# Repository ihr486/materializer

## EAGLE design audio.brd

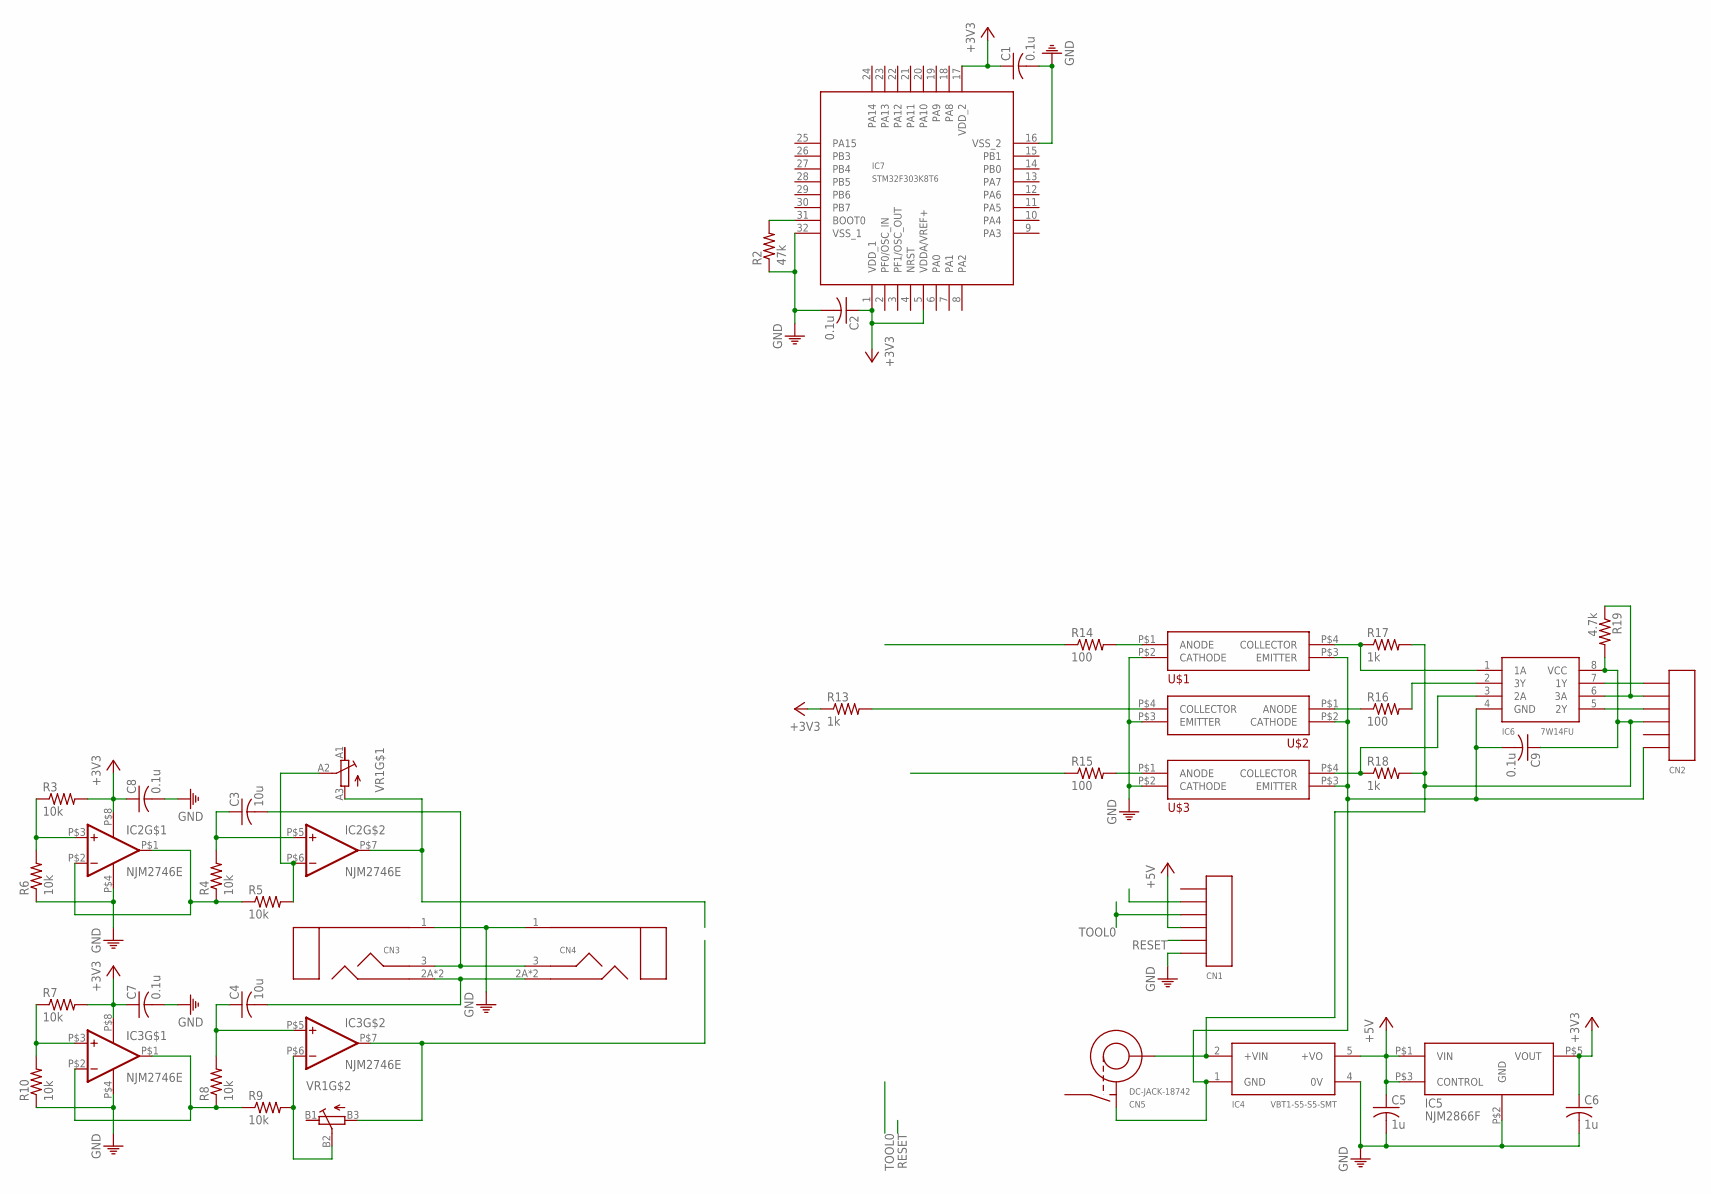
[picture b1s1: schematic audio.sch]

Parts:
C1, C2, C7, C8, C9: 0.1u; C2012
C3, C4: 10u; C2012
C5, C6: 1u; C2012
CN1: PH-1X06SG
CN2: PH-1X06RG
CN3, CN4: STEREO-3.5-MJ8435; MJ8435
CN5: DC-JACK-18742; 18742
IC2, IC3: NJM2746E; EMP8
IC4: VBT1-S5-S5-SMT
IC5: NJM2866F; SOT-23-5
IC6: 7W14FU; SSOP8-P-0.65
IC7: STM32F303K8T6; P-LQFP32-7X7-0.80
R2: 47k; R2012
R3, R4, R5, R6, R7, R8, R9, R10: 10k; R2012
R13, R17, R18: 1k; R2012
R14, R15, R16: 100; R2012
R19: 4.7k; R2012
U$1, U$2, U$3: TLP291; 11-3C1
VR1: R-TRIM-RK0971220; RK0971220-F15-C0-A104

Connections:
+3V3: C1.1, C2.1, C6.1, C7.1, C8.1, IC2.P$8 (V+), IC3.P$8 (V+), IC5.P$5 (VOUT), IC7.1 (VDD_1), IC7.5 (VDDA/VREF+), IC7.17 (VDD_2), R3.2, R7.2, R13.1
+5V: C5.1, CN1.P$4, IC4.5 (+VO), IC5.P$1 (VIN), IC5.P$3 (CONTROL)
GND: C1.2, C2.2, C5.2, C6.2, C7.2, C8.2, CN1.P$6, CN3.1 (SLEEVE), CN4.1 (SLEEVE), IC2.P$4 (V-), IC3.P$4 (V-), IC4.4 (0V), IC5.P$2 (GND), IC7.16 (VSS_2), IC7.32 (VSS_1), R2.1, R6.1, R10.1, U$1.P$2 (CATHODE), U$2.P$3 (EMITTER), U$3.P$2 (CATHODE)
unnamed: IC2.P$1 (OUT), IC2.P$2 (-IN), R4.1, R5.1
unnamed: IC7.31 (BOOT0), R2.2
unnamed: C3.2, CN3.3 (RING), CN4.3 (RING)
unnamed: C3.1, IC2.P$5 (+IN), R4.2
unnamed: IC2.P$3 (+IN), R3.1, R6.2
unnamed: C9.2, CN2.P$6, CN5.P$2 (TIP), IC4.1 (GND), IC6.4 (GND), U$1.P$3 (EMITTER), U$2.P$2 (CATHODE), U$3.P$3 (EMITTER)
unnamed: C9.1, CN2.P$4, CN5.P$1 (CENTER), IC4.2 (+VIN), IC6.8 (VCC), R17.2, R18.2, R19.2
unnamed: IC2.P$6 (-IN), R5.2, VR1.A2 (S)
unnamed: IC2.P$7 (OUT), VR1.A3 (E)
unnamed: IC3.P$1 (OUT), IC3.P$2 (-IN), R8.1, R9.1
unnamed: IC3.P$3 (+IN), R7.1, R10.2
unnamed: C4.1, IC3.P$5 (+IN), R8.2
unnamed: IC3.P$6 (-IN), R9.2, VR1.B2 (S)
unnamed: C4.2, CN3.2A (TIP), CN3.2B (TIP), CN4.2A (TIP), CN4.2B (TIP)
unnamed: IC3.P$7 (OUT), VR1.B3 (E)
unnamed: R13.2, U$2.P$4 (COLLECTOR)
unnamed: R14.2, U$1.P$1 (ANODE)
unnamed: IC6.3 (2A), R18.1, U$3.P$4 (COLLECTOR)
unnamed: R15.2, U$3.P$1 (ANODE)
unnamed: R16.1, U$2.P$1 (ANODE)
unnamed: CN2.P$1, IC6.7 (1Y)
unnamed: IC6.1 (1A), R17.1, U$1.P$4 (COLLECTOR)
unnamed: CN2.P$2, IC6.6 (3A), R19.1
unnamed: CN2.P$3, IC6.5 (2Y)
unnamed: IC6.2 (3Y), R16.2
RESET: CN1.P$5
TOOL0: CN1.P$3

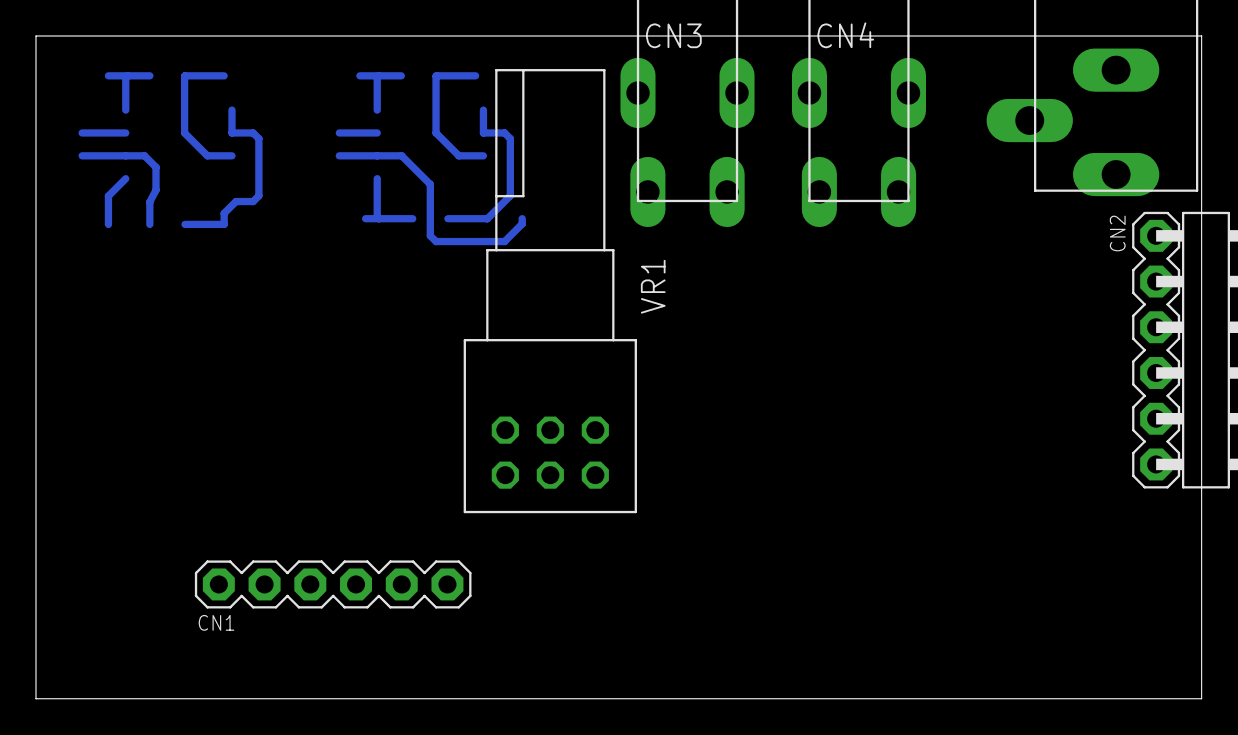
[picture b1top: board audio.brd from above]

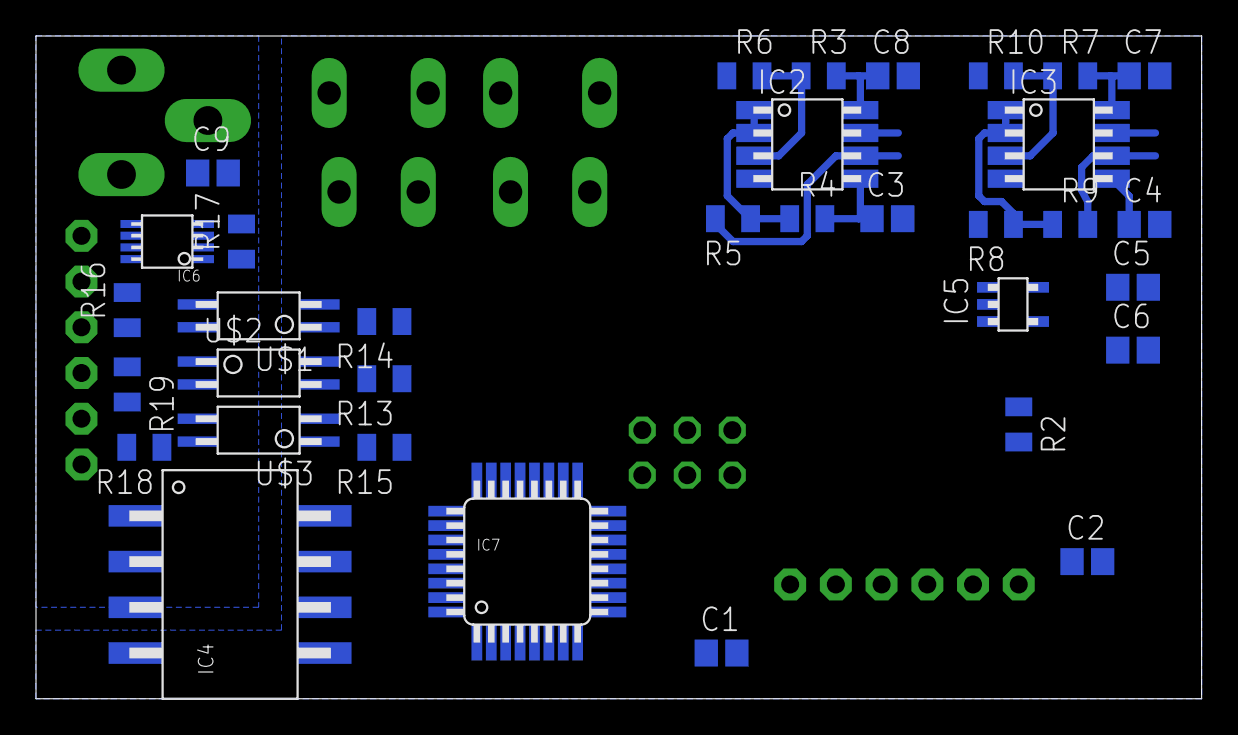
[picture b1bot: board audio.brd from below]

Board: 2 copper layers, 64.8 x 36.8 mm, 40 parts (34 on the bottom side), 28 nets.

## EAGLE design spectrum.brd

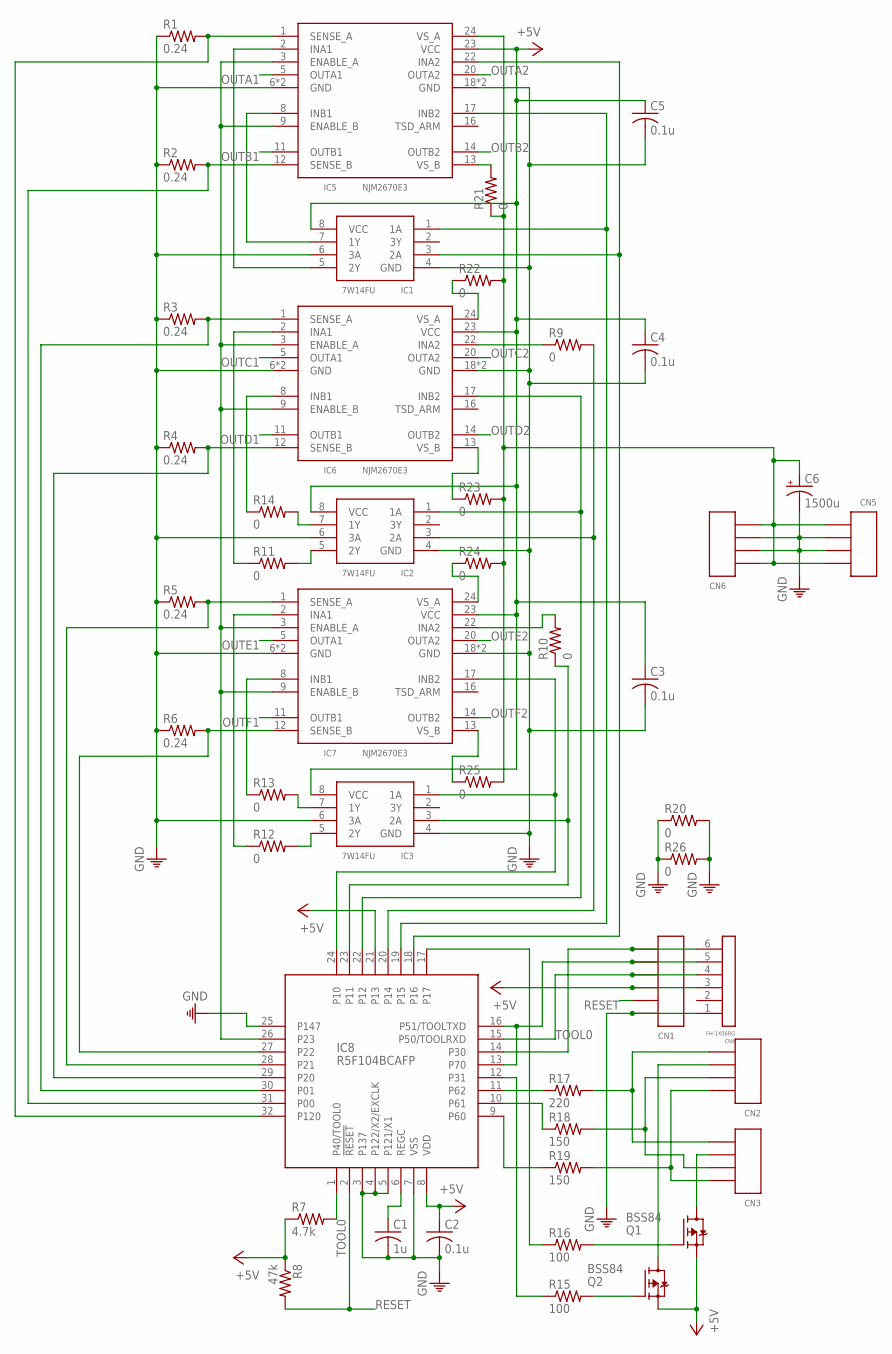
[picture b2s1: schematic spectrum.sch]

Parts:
C1: 1u; C2012
C2, C3, C4, C5: 0.1u; C2012
C6: 1500u; E3,5-8
CN1: PH-1X06RG
CN2, CN3: PH-1X04SG
CN4: FH-1X06RG
CN5: PH-1X04SGRG; PH-1X04RG
CN6: FH-1X04RG
IC1, IC2, IC3: 7W14FU; SSOP8-P-0.65
IC5, IC6, IC7: NJM2670E3; EMP-24
IC8: R5F104BCAFP; P-LQFP32-7X7-0.80
Q1, Q2: BSS84; SOT-23F
R1, R2, R3, R4, R5, R6: 0.24; R3225
R7: 4.7k; R2012
R8: 47k; R2012
R9, R10, R11, R12, R13, R14: 0; R2012
R15, R16: 100; R2012
R17: 220; R2012
R18, R19: 150; R2012
R20, R26: 0; 0204/5
R21, R22, R23, R24, R25: 0; 0204/7

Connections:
+5V: C2.1, C3.1, C4.1, C5.1, CN1.P$4, CN4.3, IC1.8 (VCC), IC2.8 (VCC), IC3.8 (VCC), IC5.23 (VCC), IC6.23 (VCC), IC7.23 (VCC), IC8.8 (VDD), IC8.21 (P13), Q1.P$2 (S), Q2.P$2 (S), R7.1, R8.1
GND: C1.2, C2.2, C3.2, C4.2, C5.2, C6.-, CN1.P$6, CN4.1, CN5.2, CN5.3, CN6.2, CN6.3, IC1.4 (GND), IC1.6 (3A), IC2.4 (GND), IC2.6 (3A), IC3.4 (GND), IC3.6 (3A), IC5.6 (GND), IC5.7 (GND), IC5.18 (GND), IC5.19 (GND), IC6.6 (GND), IC6.7 (GND), IC6.18 (GND), IC6.19 (GND), IC7.6 (GND), IC7.7 (GND), IC7.18 (GND), IC7.19 (GND), IC8.3 (P137), IC8.4 (P122/X2/EXCLK), IC8.5 (P121/X1), IC8.7 (VSS), IC8.25 (P147), R1.1, R2.1, R3.1, R4.1, R5.1, R6.1, R20.1, R20.2, R26.1, R26.2
unnamed: IC5.1 (SENSE_A), IC8.32 (P120), R1.2
unnamed: IC5.12 (SENSE_B), IC8.31 (P00), R2.2
unnamed: IC1.7 (1Y), IC5.8 (INB1)
unnamed: IC1.1 (1A), IC5.17 (INB2), IC8.19 (P15)
unnamed: IC6.1 (SENSE_A), IC8.30 (P01), R3.2
unnamed: IC6.12 (SENSE_B), IC8.29 (P20), R4.2
unnamed: IC6.22 (INA2), R9.1
unnamed: IC7.12 (SENSE_B), IC8.27 (P22), R6.2
unnamed: IC7.1 (SENSE_A), IC8.28 (P21), R5.2
unnamed: IC5.3 (ENABLE_A), IC5.9 (ENABLE_B), IC6.3 (ENABLE_A), IC6.9 (ENABLE_B), IC7.3 (ENABLE_A), IC7.9 (ENABLE_B), IC8.26 (P23)
unnamed: IC3.1 (1A), IC7.17 (INB2), IC8.24 (P10)
unnamed: IC3.3 (2A), IC8.23 (P11), R10.1
unnamed: C6.+, CN5.1, CN5.4, CN6.1, CN6.4, IC5.24 (VS_A), R21.1, R22.2, R23.2, R24.2, R25.2
unnamed: IC2.1 (1A), IC6.17 (INB2), IC8.22 (P12)
unnamed: IC2.3 (2A), IC8.20 (P14), R9.2
unnamed: IC1.3 (2A), IC5.22 (INA2), IC8.18 (P16)
unnamed: IC1.5 (2Y), IC5.2 (INA1)
unnamed: IC7.22 (INA2), R10.2
unnamed: CN1.P$2, CN4.5, IC8.13 (P70), IC8.16 (P51/TOOLTXD)
unnamed: IC6.8 (INB1), R14.1
unnamed: IC6.2 (INA1), R11.1
unnamed: CN1.P$1, CN4.6, IC8.14 (P30)
unnamed: IC7.8 (INB1), R13.1
unnamed: IC7.2 (INA1), R12.1
unnamed: IC2.5 (2Y), R11.2
unnamed: C1.1, IC8.6 (REGC)
unnamed: IC3.5 (2Y), R12.2
unnamed: IC3.7 (1Y), R13.2
unnamed: IC2.7 (1Y), R14.2
unnamed: Q2.P$1 (G), R15.2
unnamed: Q1.P$1 (G), R16.2
unnamed: IC8.11 (P62), R17.1
unnamed: CN3.P$2, Q1.P$3 (D)
unnamed: CN2.P$2, Q2.P$3 (D)
unnamed: IC8.17, R16.1
unnamed: IC8.12 (P31), R15.1
unnamed: CN2.P$1, CN3.P$1, R17.2
unnamed: CN2.P$3, CN3.P$3, R18.2
unnamed: CN2.P$4, CN3.P$4, R19.2
unnamed: IC8.10 (P61), R18.1
unnamed: IC8.9 (P60), R19.1
unnamed: IC5.13 (VS_B), R21.2
unnamed: IC6.24 (VS_A), R22.1
unnamed: IC6.13 (VS_B), R23.1
unnamed: IC7.24 (VS_A), R24.1
unnamed: IC7.13 (VS_B), R25.1
OUTA1: IC5.5 (OUTA1)
OUTA2: IC5.20 (OUTA2)
OUTB1: IC5.11 (OUTB1)
OUTB2: IC5.14 (OUTB2)
OUTC1: IC6.5 (OUTA1)
OUTC2: IC6.20 (OUTA2)
OUTD1: IC6.11 (OUTB1)
OUTD2: IC6.14 (OUTB2)
OUTE1: IC7.5 (OUTA1)
OUTE2: IC7.20 (OUTA2)
OUTF1: IC7.11 (OUTB1)
OUTF2: IC7.14 (OUTB2)
RESET: CN1.P$5, IC8.2 (!RESET!), R8.2
TOOL0: CN1.P$3, CN4.4, IC8.1 (P40/TOOL0), IC8.15 (P50/TOOLRXD), R7.2

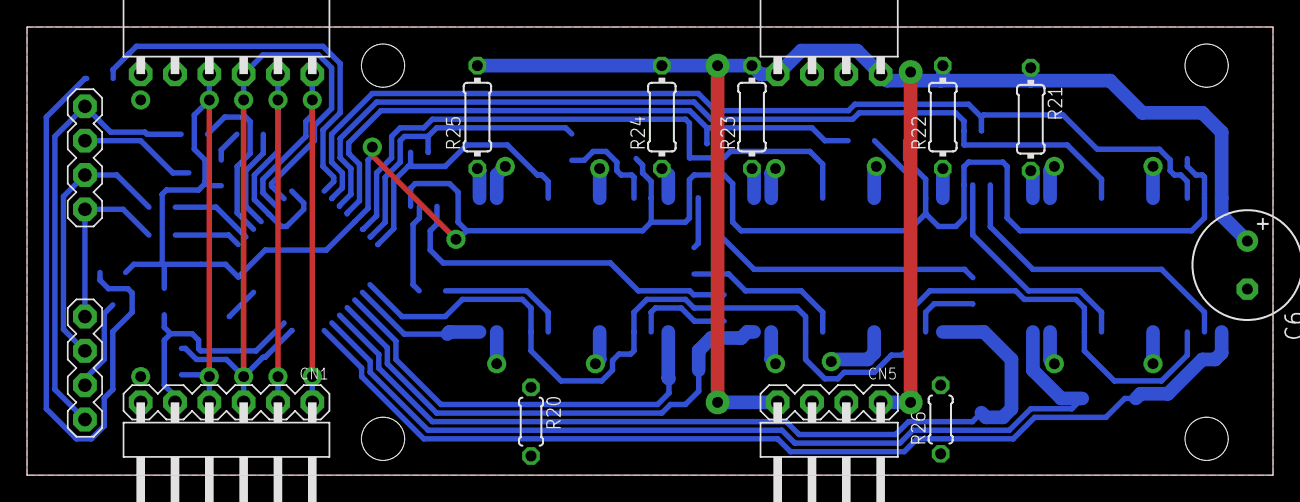
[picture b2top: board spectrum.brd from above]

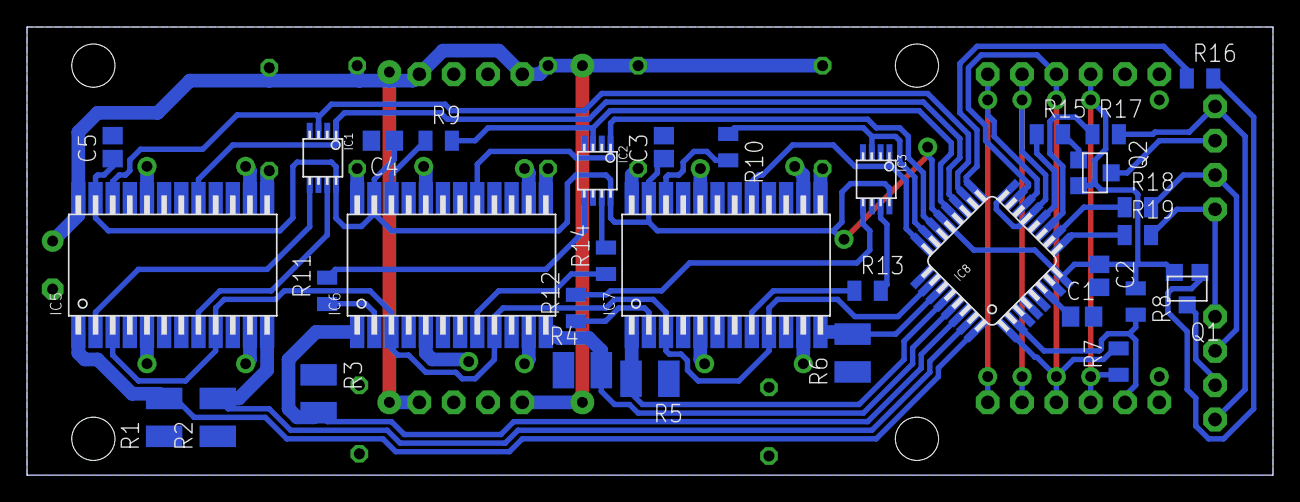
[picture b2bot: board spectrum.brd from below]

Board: 2 copper layers, 92.2 x 33.2 mm, 47 parts (33 on the bottom side), 50 nets.

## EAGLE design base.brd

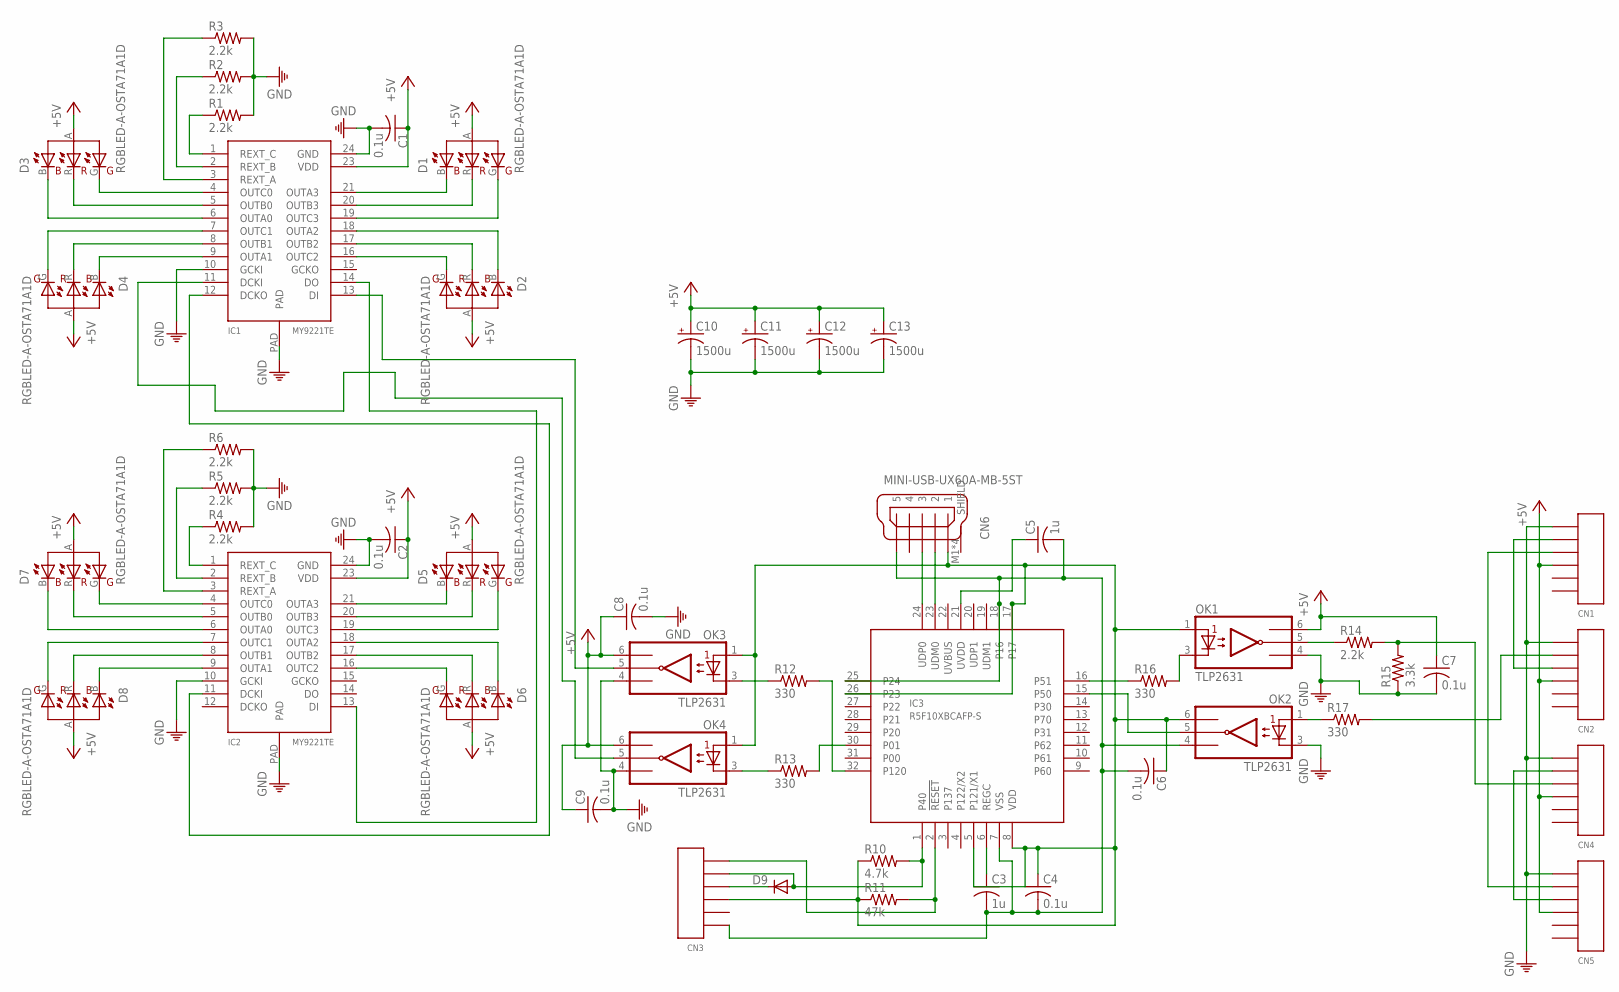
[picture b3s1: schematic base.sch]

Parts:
C1, C2, C4, C6, C7, C8, C9: 0.1u; C2012
C3, C5: 1u; C2012
C10, C11, C12, C13: 1500u; E3,5-8
CN1, CN2, CN3, CN4, CN5: PH-1X06SG
CN6: MINI-USB-UX60A-MB-5ST; UX60A-MB-5ST
D1, D2, D3, D4, D5, D6, D7, D8: RGBLED-A-OSTA71A1D; OSTA71A1D
D9: D-SOD123; SOD123
IC1, IC2: MY9221TE
IC3: R5F10XBCAFP-S; P-LQFP32-7X7-0.80S
OK1, OK2, OK3, OK4: TLP2631; 11-4L1S
R1, R2, R3, R4, R5, R6, R14: 2.2k; R2012
R10: 4.7k; R2012
R11: 47k; R2012
R12, R13, R16, R17: 330; R2012
R15: 3.3k; R2012

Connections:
+5V: C1.1, C2.1, C7.1, C8.1, C9.1, C10.+, C11.+, C12.+, C13.+, CN1.P$4, CN2.P$4, CN4.P$4, CN5.P$4, D1.A (CA), D2.A (CA), D3.A (CA), D4.A (CA), D5.A (CA), D6.A (CA), D7.A (CA), D8.A (CA), IC1.23 (VDD), IC2.23 (VDD), OK1.6 (VCC), OK3.6 (VCC), OK4.6 (VCC)
GND: C1.2, C2.2, C7.2, C8.2, C9.2, C10.-, C11.-, C12.-, C13.-, CN1.P$1, CN2.P$1, CN4.P$1, CN5.P$1, IC1.10 (GCKI), IC1.24 (GND), IC1.PAD, IC2.10 (GCKI), IC2.24 (GND), IC2.PAD, OK1.4 (GND), OK2.3 (C1), OK3.4 (GND), OK4.4 (GND), R1.2, R2.2, R3.2, R4.2, R5.2, R6.2, R15.1
unnamed: D3.G (GC), IC1.4 (OUTC0)
unnamed: D3.R (RC), IC1.5 (OUTB0)
unnamed: D3.B (BC), IC1.6 (OUTA0)
unnamed: D4.G (GC), IC1.7 (OUTC1)
unnamed: D4.R (RC), IC1.8 (OUTB1)
unnamed: D4.B (BC), IC1.9 (OUTA1)
unnamed: D2.G (GC), IC1.16 (OUTC2)
unnamed: D2.R (RC), IC1.17 (OUTB2)
unnamed: D2.B (BC), IC1.18 (OUTA2)
unnamed: D1.G (GC), IC1.19 (OUTC3)
unnamed: D1.R (RC), IC1.20 (OUTB3)
unnamed: D1.B (BC), IC1.21 (OUTA3)
unnamed: D7.G (GC), IC2.4 (OUTC0)
unnamed: IC1.1 (REXT_C), R1.1
unnamed: IC1.2 (REXT_B), R2.1
unnamed: IC1.3 (REXT_A), R3.1
unnamed: D7.R (RC), IC2.5 (OUTB0)
unnamed: D7.B (BC), IC2.6 (OUTA0)
unnamed: D8.G (GC), IC2.7 (OUTC1)
unnamed: D8.R (RC), IC2.8 (OUTB1)
unnamed: D8.B (BC), IC2.9 (OUTA1)
unnamed: D6.G (GC), IC2.16 (OUTC2)
unnamed: D6.R (RC), IC2.17 (OUTB2)
unnamed: D6.B (BC), IC2.18 (OUTA2)
unnamed: D5.G (GC), IC2.19 (OUTC3)
unnamed: D5.R (RC), IC2.20 (OUTB3)
unnamed: D5.B (BC), IC2.21 (OUTA3)
unnamed: IC2.1 (REXT_C), R4.1
unnamed: IC2.2 (REXT_B), R5.1
unnamed: IC2.3 (REXT_A), R6.1
unnamed: IC1.14 (DO), IC2.13 (DI)
unnamed: IC1.12 (DCKO), IC2.11 (DCKI)
unnamed: IC3.30 (P01), R13.2
unnamed: CN3.P$3, D9.C
unnamed: CN1.P$2, CN2.P$3
unnamed: CN2.P$2, R17.2
unnamed: CN4.P$2, CN5.P$3
unnamed: CN3.P$2, D9.A, IC3.1 (P40), R10.2
unnamed: CN1.P$3, CN5.P$2
unnamed: CN4.P$3, R14.2, R15.2
unnamed: CN6.2, IC3.23 (UDM0)
unnamed: CN6.3, IC3.24 (UDP0)
unnamed: CN3.P$1, IC3.2 (!RESET!), R11.2
unnamed: C4.1, C6.1, CN3.P$4, CN6.1, IC3.5 (P121/X1), IC3.8 (VDD), IC3.17, IC3.26 (P23), OK1.1 (A1), OK2.6 (VCC), OK3.1 (A1), OK4.1 (A1), R10.1, R11.1
unnamed: C3.1, IC3.6 (REGC)
unnamed: OK3.3 (C1), R12.1
unnamed: OK4.3 (C1), R13.1
unnamed: IC3.32 (P120), R12.2
unnamed: C3.2, C4.2, C5.2, C6.2, CN3.P$6, CN6.5, IC3.7 (VSS), IC3.18 (P16), IC3.25 (P24), OK2.4 (GND)
unnamed: IC1.11 (DCKI), OK4.5 (VO1)
unnamed: IC1.13 (DI), OK3.5 (VO1)
unnamed: C5.1, IC3.21 (UVDD)
unnamed: OK1.5 (VO1), R14.1
unnamed: OK1.3 (C1), R16.2
unnamed: IC3.15 (P50), OK2.5 (VO1)
unnamed: OK2.1 (A1), R17.1
unnamed: IC3.16 (P51), R16.1

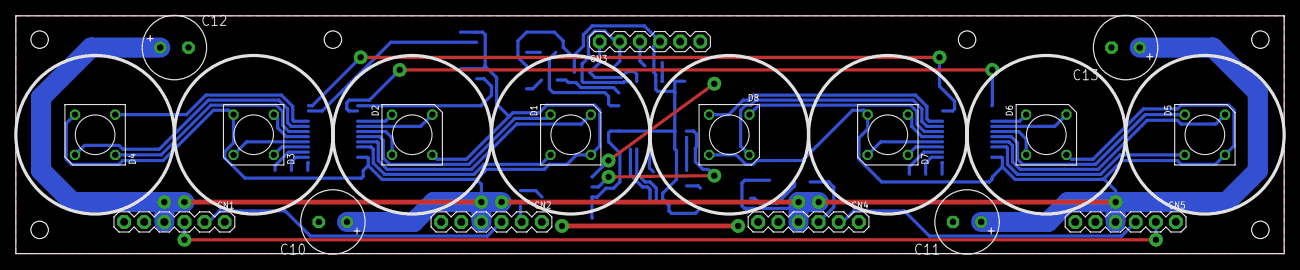
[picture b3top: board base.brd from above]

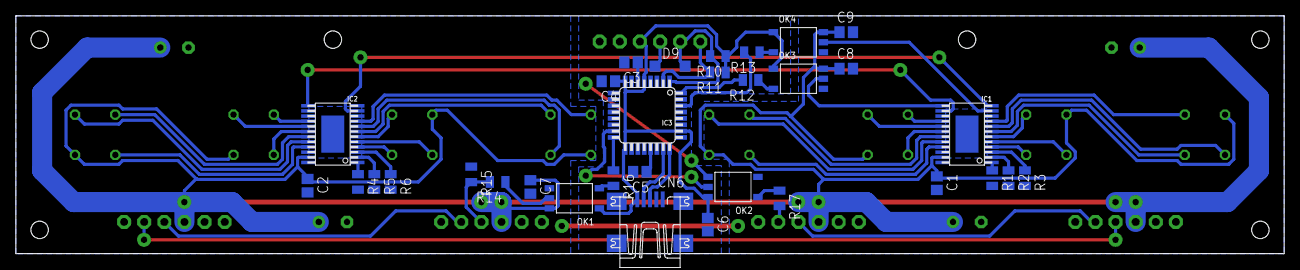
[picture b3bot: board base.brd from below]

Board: 2 copper layers, 160.0 x 30.0 mm, 49 parts (32 on the bottom side), 59 nets.

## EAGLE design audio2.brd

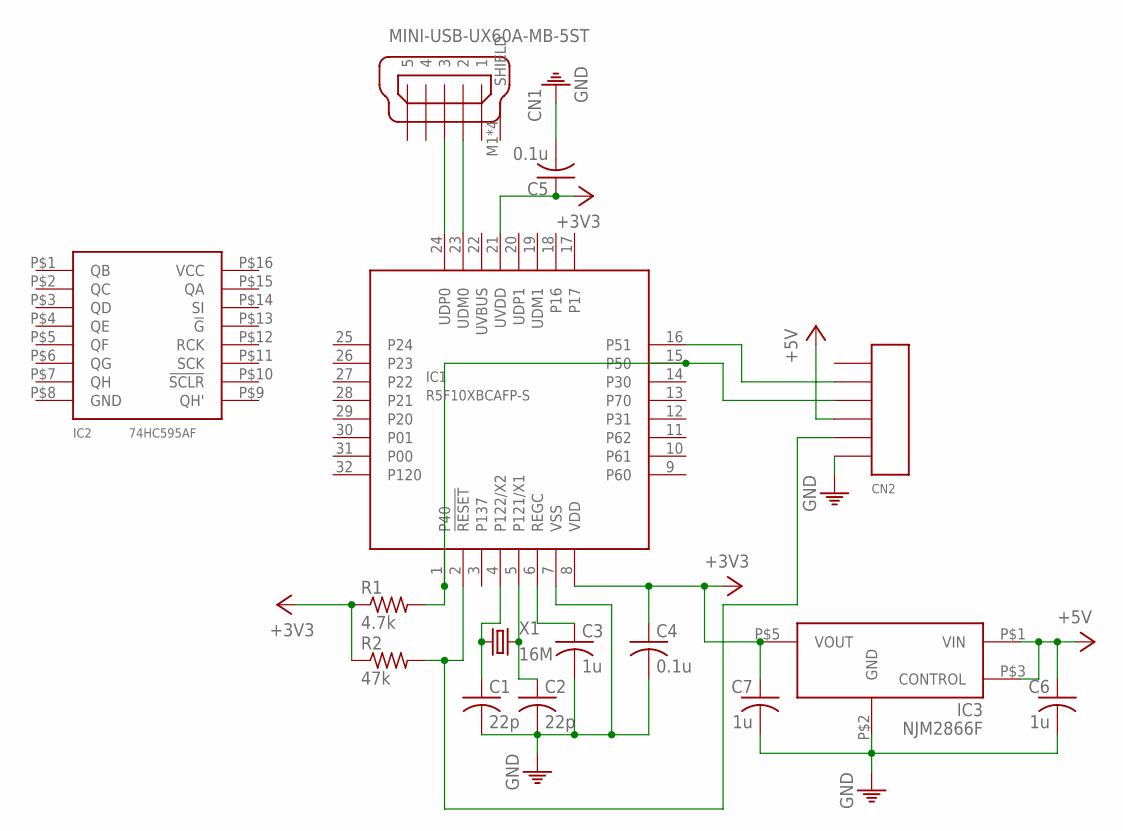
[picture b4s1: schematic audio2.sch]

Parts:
C1, C2: 22p; C1608
C3, C6, C7: 1u; C2012
C4, C5: 0.1u; C2012
CN1: MINI-USB-UX60A-MB-5ST; UX60A-MB-5ST
CN2: PH-1X06RG
IC1: R5F10XBCAFP-S; P-LQFP32-7X7-0.80S
IC2: 74HC595AF; SOP16-P-300-1.27A
IC3: NJM2866F; SOT-23-5
R1: 4.7k; R2012
R2: 47k; R2012
X1: 16M; FA-238V

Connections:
+3V3: C4.1, C5.1, C7.1, IC1.8 (VDD), IC1.21 (UVDD), IC3.P$5 (VOUT), R1.1, R2.1
+5V: C6.1, CN2.P$4, IC3.P$1 (VIN), IC3.P$3 (CONTROL)
GND: C1.2, C2.2, C3.2, C4.2, C5.2, C6.2, C7.2, CN2.P$6, IC1.7 (VSS), IC2.P$8 (GND), IC3.P$2 (GND)
unnamed: CN1.3, IC1.24 (UDP0)
unnamed: CN1.2, IC1.23 (UDM0)
unnamed: C1.1, IC1.4 (P122/X2), X1.1
unnamed: C2.1, IC1.5 (P121/X1), X1.3 (2)
unnamed: C3.1, IC1.6 (REGC)
unnamed: CN2.P$3, IC1.1 (P40), IC1.15 (P50), R1.2
unnamed: CN2.P$2, IC1.16 (P51)
unnamed: CN2.P$5, IC1.2 (!RESET!), R2.2
VCC: IC2.P$16 (VCC)

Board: 2 copper layers, 15 parts (2 on the bottom side), 11 nets, no tracks yet.

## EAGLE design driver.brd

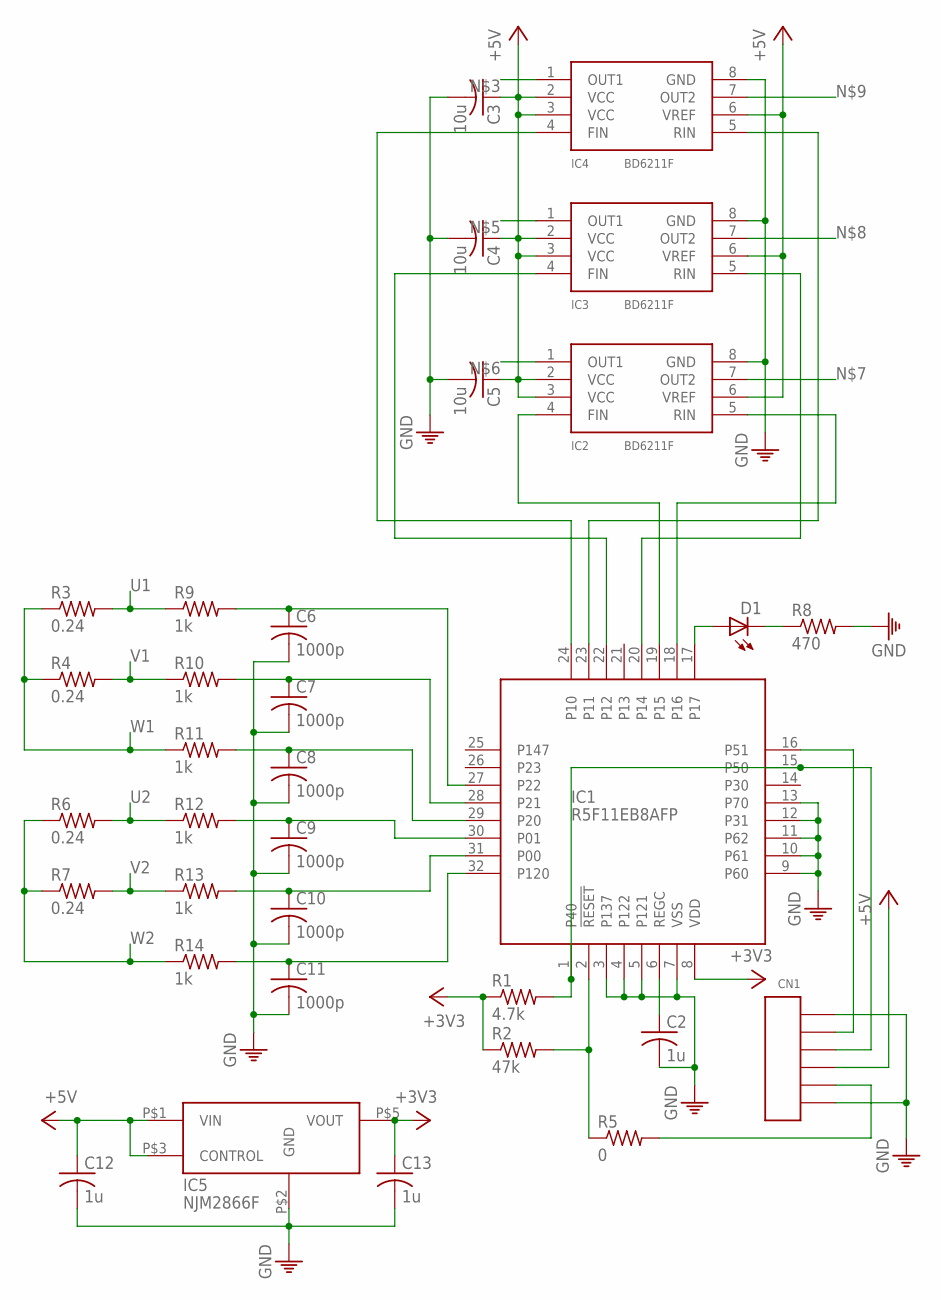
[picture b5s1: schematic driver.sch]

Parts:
C2, C12, C13: 1u; C2012
C3, C4, C5: 10u; C2012
C6, C7, C8, C9, C10, C11: 1000p; C2012
CN1: PH-1X06RG
D1: LED2012; CHIP-LED0805
IC1: R5F11EB8AFP; P-LQFP32-7X7-0.80
IC2, IC3, IC4: BD6211F; SOP8
IC5: NJM2866F; SOT-23-5
R1: 4.7k; R2012
R2: 47k; R2012
R3, R4, R6, R7: 0.24; R3225
R5: 0; R2012
R8: 470; R2012
R9, R10, R11, R12, R13, R14: 1k; R2012

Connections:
+3V3: C13.1, IC1.8 (VDD), IC5.P$5 (VOUT), R1.1, R2.1
+5V: C3.1, C4.1, C5.1, C12.1, CN1.P$3, IC2.2 (VCC), IC2.3 (VCC), IC2.6 (VREF), IC3.2 (VCC), IC3.3 (VCC), IC3.6 (VREF), IC4.2 (VCC), IC4.3 (VCC), IC4.6 (VREF), IC5.P$1 (VIN), IC5.P$3 (CONTROL)
GND: C2.2, C3.2, C4.2, C5.2, C6.2, C7.2, C8.2, C9.2, C10.2, C11.2, C12.2, C13.2, CN1.P$1, CN1.P$6, IC1.3 (P137), IC1.4 (P122), IC1.5 (P121), IC1.7 (VSS), IC1.9 (P60), IC1.10 (P61), IC1.11 (P62), IC1.12 (P31), IC1.13 (P70), IC2.8 (GND), IC3.8 (GND), IC4.8 (GND), IC5.P$2 (GND), R8.2
unnamed: C2.1, IC1.6 (REGC)
unnamed: IC1.2 (!RESET!), R2.2, R5.1
unnamed: CN1.P$4, IC1.1 (P40), IC1.15 (P50), R1.2
unnamed: IC1.19 (P15), IC2.4 (FIN)
unnamed: IC1.18 (P16), IC2.5 (RIN)
unnamed: IC1.23 (P11), IC4.5 (RIN)
unnamed: IC1.24 (P10), IC4.4 (FIN)
unnamed: C6.1, IC1.27 (P22), R9.2
unnamed: C7.1, IC1.28 (P21), R10.2
unnamed: C8.1, IC1.29 (P20), R11.2
unnamed: C9.1, IC1.30 (P01), R12.2
unnamed: C10.1, IC1.31 (P00), R13.2
unnamed: C11.1, IC1.32 (P120), R14.2
unnamed: CN1.P$5, IC1.16 (P51)
unnamed: CN1.P$2, R5.2
unnamed: D1.A, IC1.17
unnamed: IC1.22 (P12), IC3.4 (FIN)
unnamed: IC1.20 (P14), IC3.5 (RIN)
unnamed: D1.C, R8.1
U1: R3.2, R9.1
U2: R6.2, R12.1
V1: R4.2, R10.1
V2: R7.2, R13.1
W1: R3.1, R4.1, R11.1
W2: R6.1, R7.1, R14.1

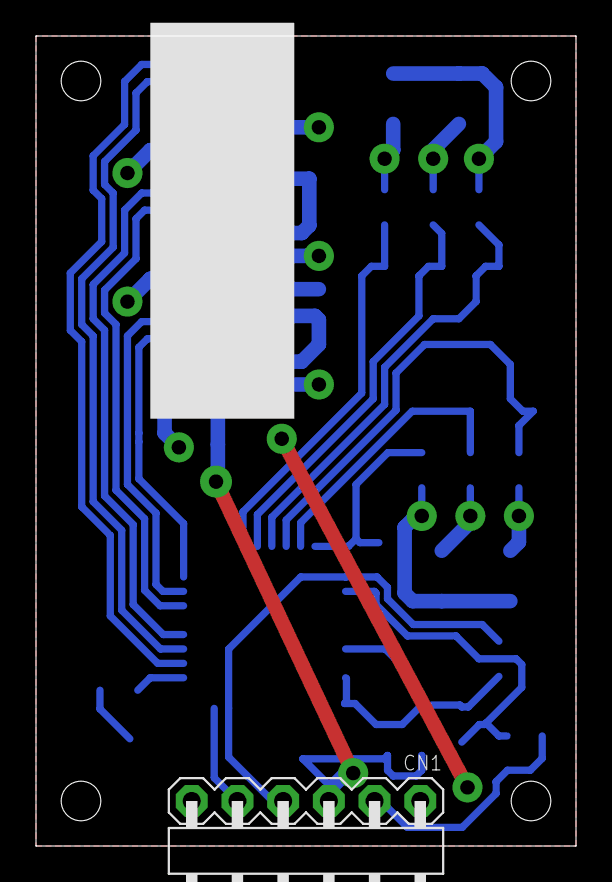
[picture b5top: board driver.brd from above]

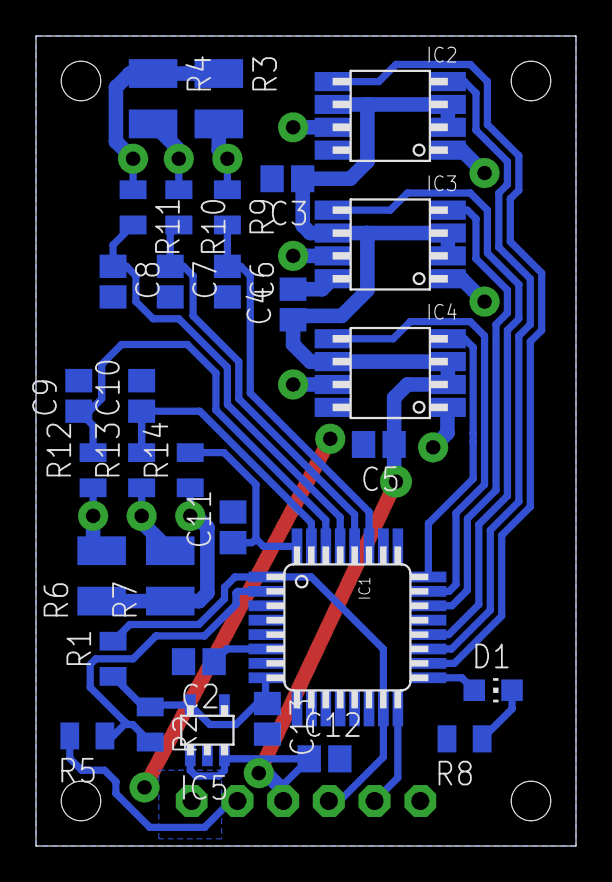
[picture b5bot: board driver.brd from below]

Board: 2 copper layers, 30.0 x 45.0 mm, 33 parts (32 on the bottom side), 28 nets.

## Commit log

2017-02-15 Added power chains
2017-02-17 Complete routing for the first time
2017-03-19 Deleted old schematics
2017-03-20 Reworked everything

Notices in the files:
parts and their libraries:
MyLib: (C) 2015 Hiroka Ihara (The University of Tokyo)
